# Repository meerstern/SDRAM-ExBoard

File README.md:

# SDRAM Extension Board
The SDRAM Extension Board of Kicad Files. 

SDRAM拡張ボードは汎用的なSDRAM TSSOP54ピンを2.54ピッチに変換するブレイクアウトボードです。
全ての信号線を等長配線しています。
電源系をまとめることで省配線化ができます。

MIT Lisense

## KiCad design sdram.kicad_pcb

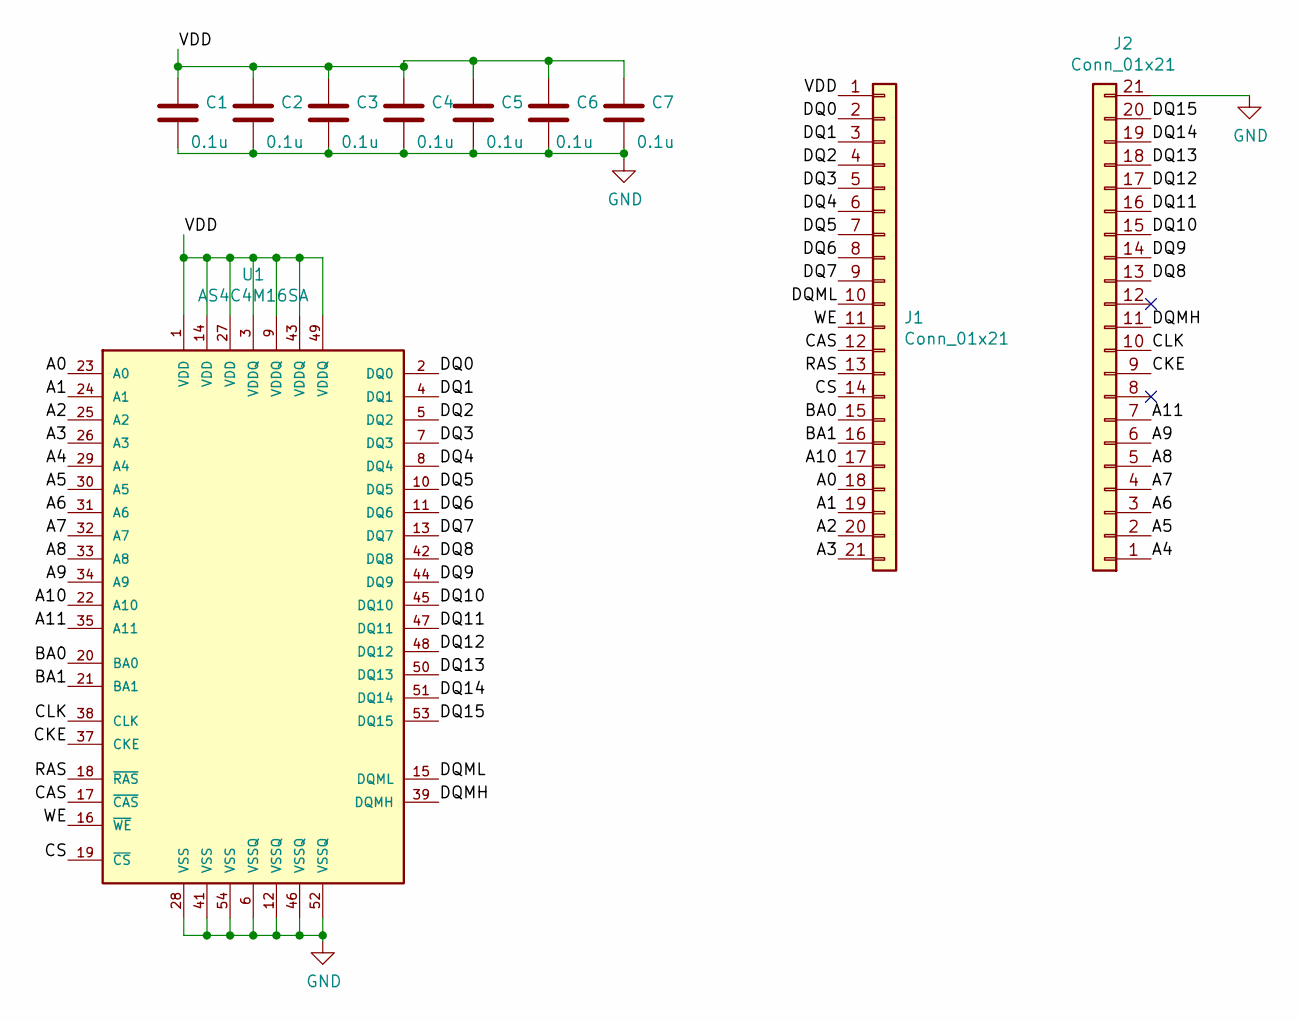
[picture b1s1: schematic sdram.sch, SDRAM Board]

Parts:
C1, C2, C3, C4, C5, C6, C7: 0.1u; generic-SMD1608
J1, J2: Conn_01x21; pinhead-1X22
U1: AS4C4M16SA; TSOP-54

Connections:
/A0: J1.18, U1.23 (A0)
/A1: J1.19, U1.24 (A1)
/A2: J1.20, U1.25 (A2)
/A3: J1.21, U1.26 (A3)
/A4: J2.1, U1.29 (A4)
/A5: J2.2, U1.30 (A5)
/A6: J2.3, U1.31 (A6)
/A7: J2.4, U1.32 (A7)
/A8: J2.5, U1.33 (A8)
/A9: J2.6, U1.34 (A9)
/A10: J1.17, U1.22 (A10)
/A11: J2.7, U1.35 (A11)
/BA0: J1.15, U1.20 (BA0)
/BA1: J1.16, U1.21 (BA1)
/CAS: J1.12, U1.17 (~CAS~)
/CKE: J2.9, U1.37 (CKE)
/CLK: J2.10, U1.38 (CLK)
/CS: J1.14, U1.19 (~CS~)
/DQ0: J1.2, U1.2 (DQ0)
/DQ1: J1.3, U1.4 (DQ1)
/DQ2: J1.4, U1.5 (DQ2)
/DQ3: J1.5, U1.7 (DQ3)
/DQ4: J1.6, U1.8 (DQ4)
/DQ5: J1.7, U1.10 (DQ5)
/DQ6: J1.8, U1.11 (DQ6)
/DQ7: J1.9, U1.13 (DQ7)
/DQ8: J2.13, U1.42 (DQ8)
/DQ9: J2.14, U1.44 (DQ9)
/DQ10: J2.15, U1.45 (DQ10)
/DQ11: J2.16, U1.47 (DQ11)
/DQ12: J2.17, U1.48 (DQ12)
/DQ13: J2.18, U1.50 (DQ13)
/DQ14: J2.19, U1.51 (DQ14)
/DQ15: J2.20, U1.53 (DQ15)
/DQMH: J2.11, U1.39 (DQMH)
/DQML: J1.10, U1.15 (DQML)
/RAS: J1.13, U1.18 (~RAS~)
/VDD: C1.1, C2.1, C3.1, C4.1, C5.1, C6.1, C7.1, J1.1, U1.1 (VDD), U1.3 (VDDQ), U1.9 (VDDQ), U1.14 (VDD), U1.27 (VDD), U1.43 (VDDQ), U1.49 (VDDQ)
/WE: J1.11, U1.16 (~WE~)
GND: C1.2, C2.2, C3.2, C4.2, C5.2, C6.2, C7.2, J2.21, U1.6 (VSSQ), U1.12 (VSSQ), U1.28 (VSS), U1.41 (VSS), U1.46 (VSSQ), U1.52 (VSSQ), U1.54 (VSS)

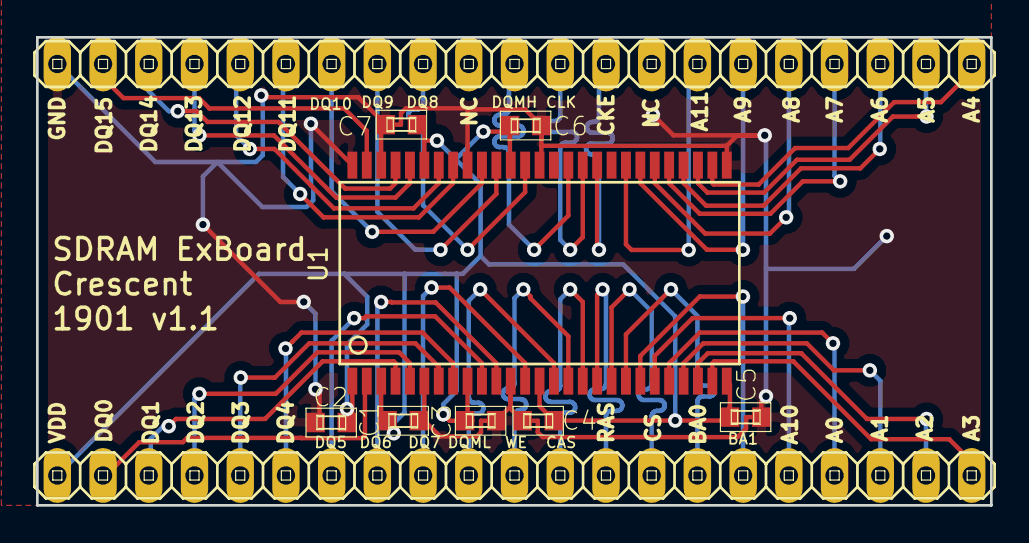
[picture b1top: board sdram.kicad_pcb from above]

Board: 2 copper layers, 53.0 x 26.0 mm, 10 parts (0 on the bottom side), 40 nets.

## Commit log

2019-01-05 v1.1
2019-01-05 Add Figure
